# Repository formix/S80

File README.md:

# S80
## S80 - Stackable retro Z80 computer
Welcome to the primary source of information regarding the S80.

For in depth information on the S80 hardware, please visit: [S80 website](http://users.telenet.be/pynckels/s80_retro.html)

The S80 facebook page can be found at: [S80 on Facebook](https://www.facebook.com/S80computer)

The issues section of this repository will serve as discussion forum on everything around the S80 (actual and future hardware, actual and future software, inspirational ideas, questions, ...): [S80 community and forum](https://github.com/PaintedBlck/S80/issues)

We hope this is the beginning of a growing community of people around the S80 who want to inspire others, learn, help, discuss, ... See also the Code of Conduct, since this document describes how we see collaboration and having fun.

## S80C - Small Z80 Cp/m computer

This is a project in the making. The first discussions on the functionality have begun on the [S80 community and forum in Issue 12](https://github.com/PaintedBlck/S80/issues/12).

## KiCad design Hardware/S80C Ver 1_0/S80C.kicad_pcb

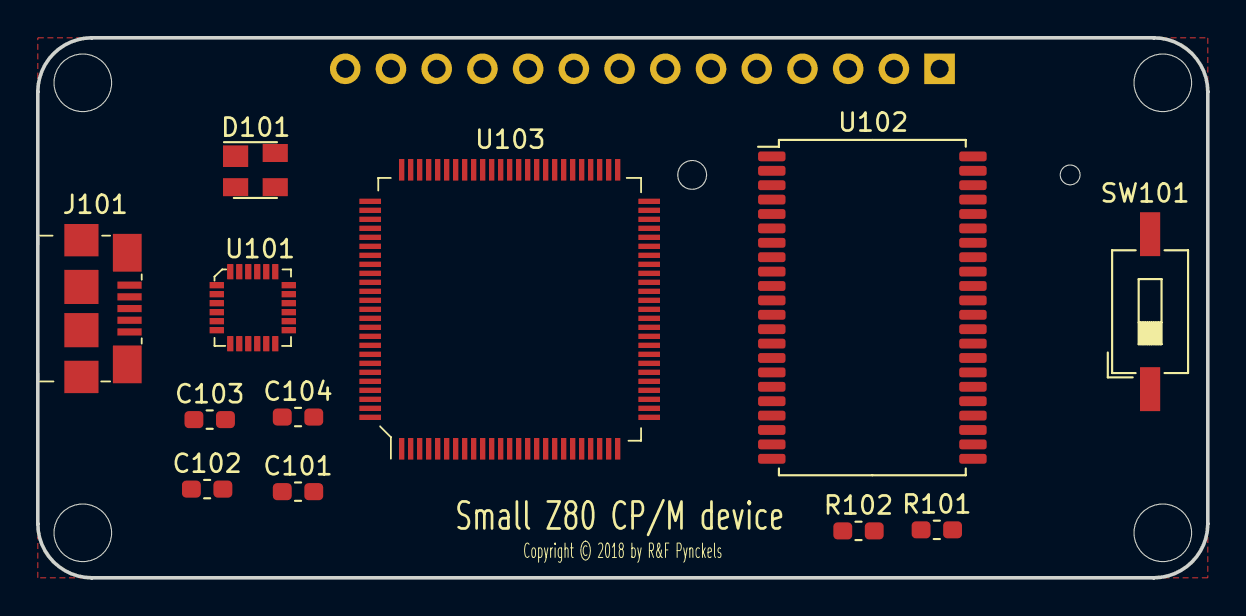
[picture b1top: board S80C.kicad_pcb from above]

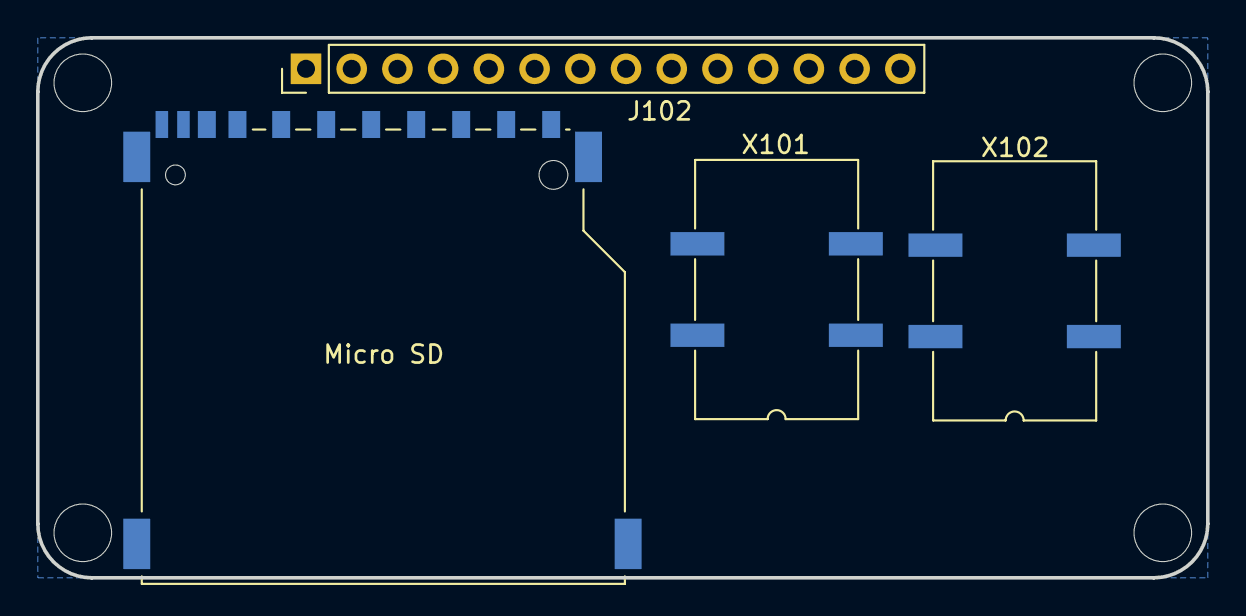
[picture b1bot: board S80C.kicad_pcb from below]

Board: 2 copper layers, 65.0 x 30.0 mm, 16 parts (4 on the bottom side), 64 nets, no tracks yet.

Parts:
C101: 22µF; C_0603_1608Metric_Pad1.05x0.95mm_HandSolder
C102: 2µF; C_0603_1608Metric_Pad1.05x0.95mm_HandSolder
C103: 0.1µF; C_0603_1608Metric_Pad1.05x0.95mm_HandSolder
C104: 1µF; C_0603_1608Metric_Pad1.05x0.95mm_HandSolder
D101: SP0503BAHT; SOT-143
J101: USB; USB_Micro_B_Female_10118192
J102: Conn_01x14_Male; PinHeader_1x14_P2.54mm_Vertical
Micro SD: SD_TE_2041021
R101, R102: 1K 5%; R_0603_1608Metric_Pad1.05x0.95mm_HandSolder
SW101: SW_Push; SW_DIP_SPSTx01_Slide_6.7x4.1mm_W8.61mm_P2.54mm_LowProfile
U101: CP2105; QFN-24-1EP_4x4mm
U102: AS6C8008A; TSOP-II-44_10.16x18.41mm_P0.8mm
U103: eZ80L92; LQFP-100_14x14mm
X101: SG-615PTJ 32Khz; Oscillator_SMD_SeikoEpson_SG8002JA-4Pin_14.0x8.7mm
X102: SG-615PTJ 50Mhz; Oscillator_SMD_SeikoEpson_SG8002JA-4Pin_14.0x8.7mm

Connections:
+3V3: C102.1, C103.1, U101.5, U101.6
/A0: U102.5, U103.1
/A1: U102.4, U103.2
/A2: U102.3, U103.3
/A3: U102.2, U103.4
/A4: U102.1, U103.5
/A5: U102.44, U103.6
/A6: U102.43, U103.9
/A7: U102.42, U103.10
/A8: U102.39, U103.11
/A9: U102.28, U103.12
/A10: U102.27, U103.13
/A11: U102.26, U103.14
/A12: U102.25, U103.15
/A13: U102.24, U103.16
/A14: U102.23, U103.17
/A15: U102.22, U103.20
/A16: U102.21, U103.21
/A17: U102.20, U103.22
/A18: U102.19, U103.23
/A19: U102.18, U103.24
/CTSe: U101.10, U103.78
/CTSs: U101.18, U103.70
/D0: U102.9, U103.35
/D1: U102.10, U103.36
/D2: U102.13, U103.37
/D3: U102.14, U103.38
/D4: U102.31, U103.39
/D5: U102.32, U103.40
/D6: U102.35, U103.41
/D7: U102.36, U103.42
/DSRe: U101.14, U103.80
/DSRs: U101.22, U103.72
/DTRe: U101.15, U103.81
/DTRs: U101.23, U103.73
/GPIO0: J102.3, U103.88
/GPIO1: J102.4, U103.89
/GPIO2: J102.5, U103.90
/GPIO3: J102.6, U103.91
/GPIO4: J102.7, U103.92
/GPIO5: J102.8, U103.93
/GPIO6: J102.9, U103.94
/GPIO7: J102.10, U103.95
/PC6: J102.11, U103.82
/PC7: J102.12, U103.83
/PD6: J102.13, U103.74
/PD7: J102.14, U103.75
/RTC_XIN: U103.58, X101.3
/RTSe: U101.11, U103.79
/RTSs: U101.19, U103.71
/RxDe: U101.12, U103.76
/RxDs: U101.20, U103.68
/TxDe: U101.13, U103.77
/TxDs: U101.21, U103.69
/XIN: U103.85, X102.3
/~MREQ: U102.6, U103.46
/~RESET: C101.1, R102.1, U101.9, U103.51
/~WR: U102.17, U103.48
GND: C101.2, C102.2, C103.2, C104.2, J101.5, J102.2, SW101.1, U101.2, U102.12, U102.34, U103.8, U103.19, U103.34, U103.44, U103.57, U103.61, U103.84, U103.97, X101.2, X102.2
unnamed: D101.1, J101.4
unnamed: D101.2, J101.2, U101.4
unnamed: D101.3, J101.3, U101.3
unnamed: R101.1, R102.2, SW101.2
VCC: C104.1, D101.4, J101.1, J102.1, R101.2, U101.7, U101.8, U102.11, U102.33, U102.40, U103.7, U103.18, U103.33, U103.43, U103.56, U103.60, U103.67, U103.87, U103.96, X101.1, X101.4, X102.1, X102.4

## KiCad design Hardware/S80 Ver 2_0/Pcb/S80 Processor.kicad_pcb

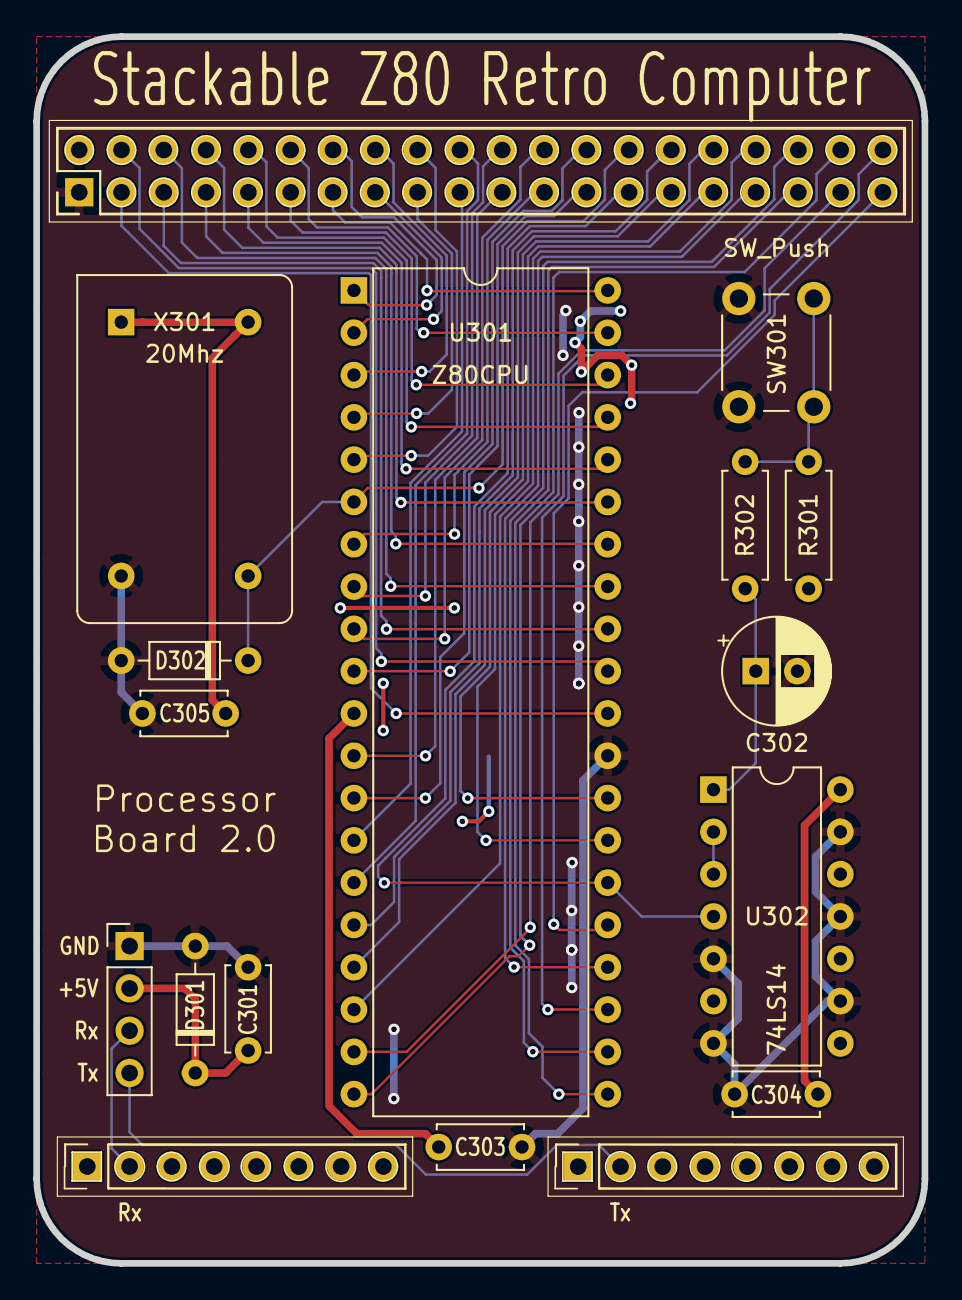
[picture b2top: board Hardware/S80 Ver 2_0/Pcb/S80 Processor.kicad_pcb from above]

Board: 2 copper layers, 53.3 x 73.7 mm, 17 parts (0 on the bottom side), 45 nets.

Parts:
C301, C303, C304, C305: 100pf; C_Disc_D5.0mm_W2.5mm_P5.00mm
C302: 22μF; CP_Radial_D6.3mm_P2.50mm
D301, D302: 5V1; D_Zener_Reverse_Biased
J301, J303: 01x08; PinSocket_1x08_P2.54mm_Vertical
J302: 02x20; PinSocket_2x20_P2.54mm_Vertical
J304: 01x04; PinHeader_1x04_P2.54mm_Vertical
R301, R302: 1K 5%; R_Axial_DIN0207_L6.3mm_D2.5mm_P7.62mm_Horizontal
SW301: SW_Push; SW_PUSH_6mm
U301: Z80CPU; DIP-40_W15.24mm
U302: 74LS14; DIP-14_W7.62mm
X301: 20Mhz; Oscillator_DIP-14

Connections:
/Memory/A0: J302.3, U301.30
/Memory/A1: J302.4, U301.31
/Memory/A2: J302.5, U301.32
/Memory/A3: J302.6, U301.33
/Memory/A4: J302.7, U301.34
/Memory/A5: J302.8, U301.35
/Memory/A6: J302.9, U301.36
/Memory/A7: J302.10, U301.37
/Memory/A8: J302.11, U301.38
/Memory/A9: J302.12, U301.39
/Memory/A10: J302.13, U301.40
/Memory/A11: J302.14, U301.1
/Memory/A12: J302.15, U301.2
/Memory/A13: J302.16, U301.3
/Memory/A14: J302.17, U301.4
/Memory/A15: J302.18, U301.5
/Memory/C8: J302.35, U301.21
/Memory/C9: J302.36, U301.22
/Memory/C10: J302.37, U301.19
/Memory/D0: J302.19, U301.14
/Memory/D1: J302.20, U301.15
/Memory/D2: J302.21, U301.12
/Memory/D3: J302.22, U301.8
/Memory/D4: J302.23, U301.7
/Memory/D5: J302.24, U301.9
/Memory/D6: J302.25, U301.10
/Memory/D7: J302.26, U301.13
/Processor/C0: J302.27, U301.26, U302.4
/Processor/C1: D302.2, J302.28, U301.6, X301.8
/Processor/C2: J302.29, U301.17
/Processor/C3: J302.30, U301.16
/Processor/C4: J302.31, U301.27
/Processor/C5: J302.32, U301.28
/Processor/C6: J302.33, U301.24
/Processor/C7: J302.34, U301.18
/Processor/C11: J302.38, U301.20
/Processor/C12: J302.39, U301.25
/Processor/C13: J302.40, U301.23
/Processor/Rx: J301.2, J304.3
/Processor/Tx: J303.2, J304.4
GND: C301.1, C302.2, C303.1, C304.1, C305.1, D301.1, D302.1, J302.1, J304.1, SW301.1, U301.29, U302.5, U302.7, U302.9, U302.11, U302.13, X301.7
unnamed: C302.1, R302.1, U302.1
unnamed: R301.2, R302.2, SW301.2
unnamed: U302.2, U302.3
VCC: C301.2, C303.2, C304.2, C305.2, D301.2, J302.2, J304.2, R301.1, U301.11, U302.14, X301.1, X301.14

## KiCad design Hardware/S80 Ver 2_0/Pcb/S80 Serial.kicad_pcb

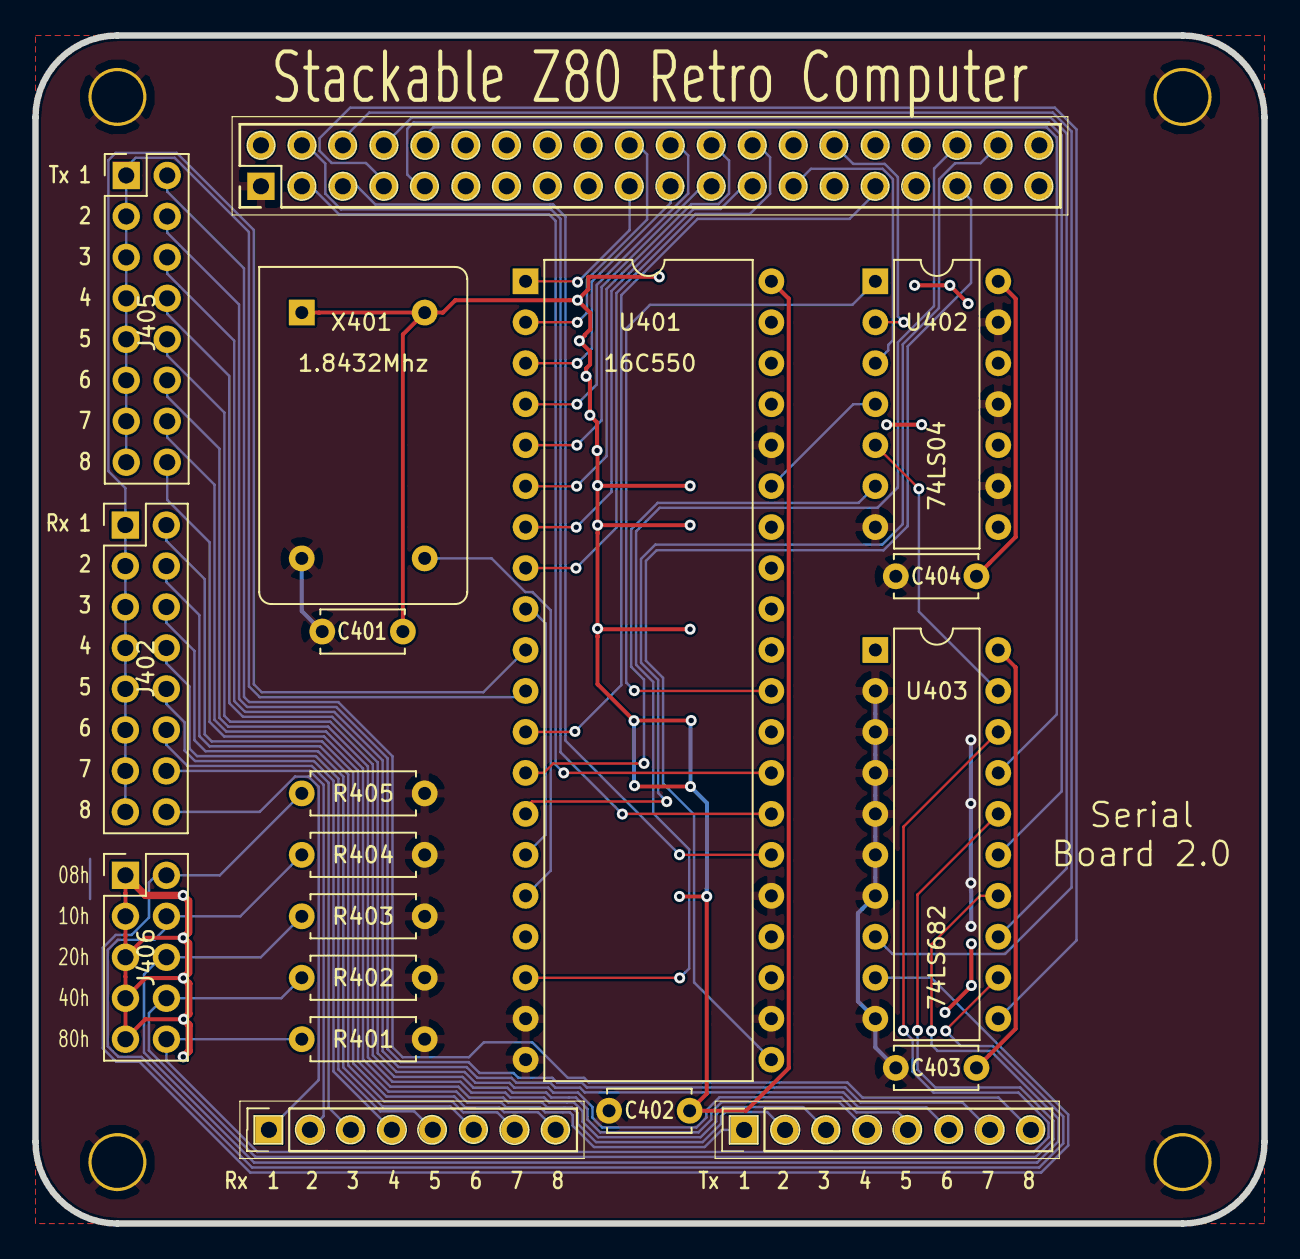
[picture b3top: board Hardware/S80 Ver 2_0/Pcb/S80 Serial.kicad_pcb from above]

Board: 2 copper layers, 76.2 x 73.7 mm, 23 parts (0 on the bottom side), 53 nets.

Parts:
C401, C402, C403, C404: 100pf; C_Disc_D5.0mm_W2.5mm_P5.00mm
H401, H402, H403, H404: Mh_Pad; MountingHole_3.2mm_Via
J401, J404: 01x08; PinSocket_1x08_P2.54mm_Vertical
J402, J405: 02x08; PinHeader_2x08_P2.54mm_Vertical
J403: 02x20; PinSocket_2x20_P2.54mm_Vertical
J406: 02x05; PinHeader_2x05_P2.54mm_Vertical
R401, R402, R403, R404, R405: 5K 5%; R_Axial_DIN0207_L6.3mm_D2.5mm_P7.62mm_Horizontal
U401: 16C550; DIP-40_W15.24mm
U402: 74LS04; DIP-14_W7.62mm
U403: 74LS682; DIP-20_W7.62mm
X401: 1.8432Mhz; Oscillator_DIP-14

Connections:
/Memory/A0: J403.3, U401.28
/Memory/A1: J403.4, U401.27
/Memory/A2: J403.5, U401.26
/Memory/A3: J403.6, U403.8
/Memory/A4: J403.7, U403.11
/Memory/A5: J403.8, U403.13
/Memory/A6: J403.9, U403.15
/Memory/A7: J403.10, U403.17
/Memory/C8: J403.35, U401.21
/Memory/C9: J403.36, U401.18
/Memory/D0: J403.19, U401.1
/Memory/D1: J403.20, U401.2
/Memory/D2: J403.21, U401.3
/Memory/D3: J403.22, U401.4
/Memory/D4: J403.23, U401.5
/Memory/D5: J403.24, U401.6
/Memory/D6: J403.25, U401.7
/Memory/D7: J403.26, U401.8
/Processor/C0: J403.27, U402.3
/Processor/C3: J403.30, U402.2
/Processor/C4: J403.31, U401.12
/Processor/C11: J403.38, U401.14
/Processor/Rx: J402.1, J402.3, J402.5, J402.7, J402.9, J402.11, J402.13, J402.15, U401.10
/Processor/Tx: J405.1, J405.3, J405.5, J405.7, J405.9, J405.11, J405.13, J405.15, U401.11
GND: C401.1, C402.1, C403.1, C404.1, H401.1, H402.1, H403.1, H404.1, J403.1, R401.2, R402.2, R403.2, R404.2, R405.2, U401.19, U401.20, U401.22, U401.25, U401.36, U402.7, U402.9, U402.11, U402.13, U403.2, U403.3, U403.4, U403.5, U403.6, U403.7, U403.10, X401.7
unnamed: J401.1, J402.16
unnamed: J401.2, J402.14
unnamed: J401.3, J402.12
unnamed: J401.4, J402.10
unnamed: J401.5, J402.8
unnamed: J401.6, J402.6
unnamed: J401.7, J402.4
unnamed: J401.8, J402.2
unnamed: J404.1, J405.16
unnamed: J404.2, J405.14
unnamed: J404.3, J405.12
unnamed: J404.4, J405.10
unnamed: J404.5, J405.8
unnamed: J404.6, J405.6
unnamed: J404.7, J405.4
unnamed: J404.8, J405.2
unnamed: J406.2, R405.1, U403.9
unnamed: J406.4, R404.1, U403.12
unnamed: J406.6, R403.1, U403.14
unnamed: J406.8, R402.1, U403.16
unnamed: J406.10, R401.1, U403.18
unnamed: U401.13, U402.6
unnamed: U401.9, U401.15
unnamed: U401.16, X401.8
unnamed: U401.30, U402.1
unnamed: U401.35, U402.4
unnamed: U402.5, U403.19
VCC: C401.2, C402.2, C403.2, C404.2, J403.2, J406.1, J406.3, J406.5, J406.7, J406.9, U401.40, U402.14, U403.20, X401.1, X401.14

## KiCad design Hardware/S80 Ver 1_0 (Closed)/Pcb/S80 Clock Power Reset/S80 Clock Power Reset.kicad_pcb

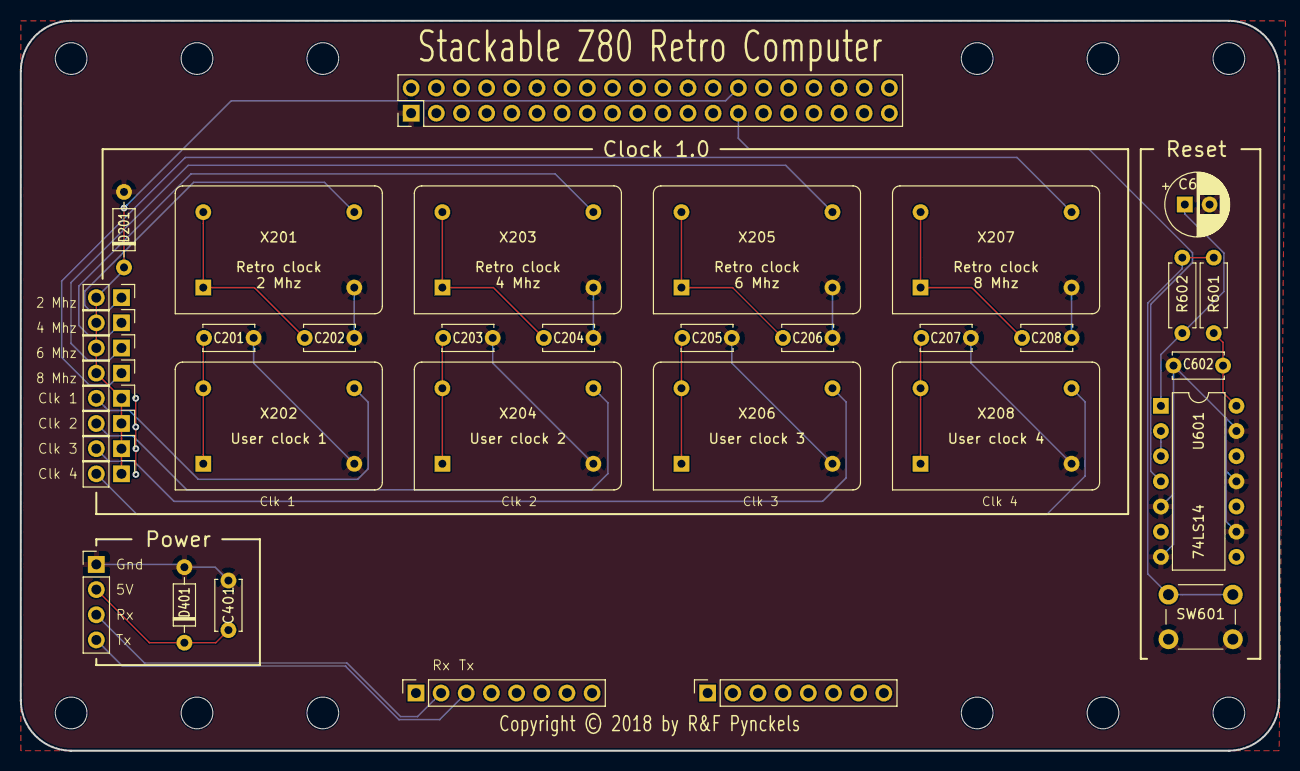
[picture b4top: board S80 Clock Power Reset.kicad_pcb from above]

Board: 2 copper layers, 127.0 x 73.7 mm, 37 parts (0 on the bottom side), 17 nets.

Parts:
C201, C202, C203, C204, C205, C206, C207, C208, C401, C602: 100pf; C_Disc_D5.0mm_W2.5mm_P5.00mm
C601: 22μF; CP_Radial_D6.3mm_P2.50mm
D201, D401: 5V1; D_Zener_Reverse_Biased
J201: 02x20; PinSocket_2x20_P2.54mm_Vertical
J402, J403: 01x08; PinSocket_1x08_P2.54mm_Vertical
J404: 01x04; PinHeader_1x04_P2.54mm_Vertical
JP201, JP202, JP203, JP204, JP205, JP206, JP207, JP208: 01x02; PinHeader_1x02_P2.54mm_Vertical
R601, R602: 1K; R_Axial_DIN0207_L6.3mm_D2.5mm_P7.62mm_Horizontal
SW601: SW_Push; SW_PUSH_6mm
U601: 74LS14; DIP-14_W7.62mm
X201: 2.5Mhz; Oscillator_DIP-14
X202: User clk 1; Oscillator_DIP-14
X203: 4Mhz; Oscillator_DIP-14
X204: User clk 2; Oscillator_DIP-14
X205: 6Mhz; Oscillator_DIP-14
X206: User clk 3; Oscillator_DIP-14
X207: 8Mhz; Oscillator_DIP-14
X208: User clk 4; Oscillator_DIP-14

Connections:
/Breakout 2in/C0: J201.27, U601.4
/Breakout 2in/C1: D201.2, J201.28, JP201.2, JP202.1, JP203.2, JP204.1, JP205.2, JP206.1, JP207.2, JP208.1
/Power/Rx: J402.2, J404.3
/Power/Tx: J402.3, J404.4
GND: C201.1, C202.1, C203.1, C204.1, C205.1, C206.1, C207.1, C208.1, C401.1, C601.2, C602.1, D201.1, D401.1, J201.1, J404.1, SW601.1, U601.5, U601.7, U601.9, U601.11, U601.13, X201.7, X202.7, X203.7, X204.7, X205.7, X206.7, X207.7, X208.7
unnamed: C601.1, R602.1, U601.1
unnamed: JP201.1, X201.8
unnamed: JP202.2, X202.8
unnamed: JP203.1, X203.8
unnamed: JP204.2, X204.8
unnamed: JP205.1, X205.8
unnamed: JP206.2, X206.8
unnamed: JP207.1, X207.8
unnamed: JP208.2, X208.8
unnamed: R601.2, R602.2, SW601.2
unnamed: U601.2, U601.3
VCC: C201.2, C202.2, C203.2, C204.2, C205.2, C206.2, C207.2, C208.2, C401.2, C602.2, D401.2, J201.2, J404.2, R601.1, U601.14, X201.1, X201.14, X202.1, X202.14, X203.1, X203.14, X204.1, X204.14, X205.1, X205.14, X206.1, X206.14, X207.1, X207.14, X208.1, X208.14

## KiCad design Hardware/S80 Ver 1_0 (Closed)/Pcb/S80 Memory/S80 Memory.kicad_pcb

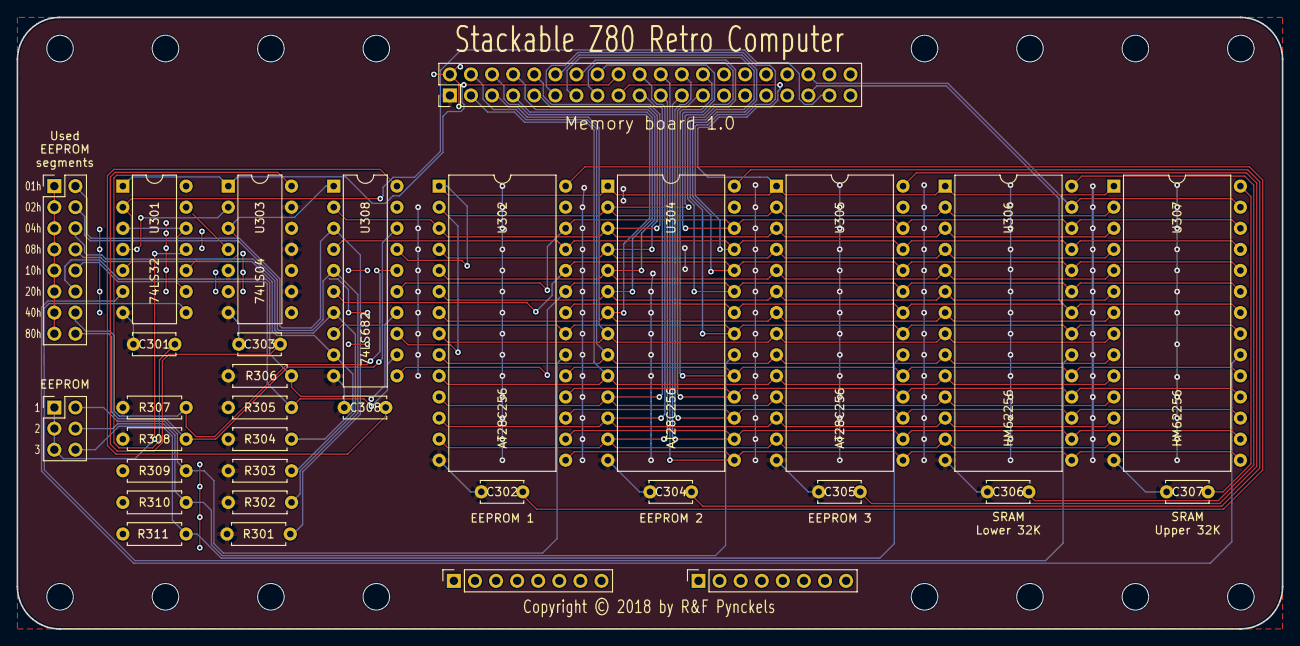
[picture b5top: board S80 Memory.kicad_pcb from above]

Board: 2 copper layers, 152.4 x 73.7 mm, 32 parts (0 on the bottom side), 47 nets.

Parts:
C301, C302, C303, C304, C305, C306, C307, C308: 100pf; C_Disc_D5.0mm_W2.5mm_P5.00mm
J301: 02x20; PinSocket_2x20_P2.54mm_Vertical
J302, J303: 01x08; PinSocket_1x08_P2.54mm_Vertical
J304: 02x08; PinHeader_2x08_P2.54mm_Vertical
J305: 02x03; PinHeader_2x03_P2.54mm_Vertical
R301, R302, R303, R304, R305, R306, R307, R308: 220 5%; R_Axial_DIN0207_L6.3mm_D2.5mm_P7.62mm_Horizontal
R309, R310, R311: 5K 1%; R_Axial_DIN0207_L6.3mm_D2.5mm_P7.62mm_Horizontal
U301: 74LS32; DIP-14_W7.62mm
U302, U304, U305: AT28C256; DIP-28_W15.24mm
U303: 74LS04; DIP-14_W7.62mm
U306, U307: HM62256; DIP-28_W15.24mm
U308: 74LS682; DIP-20_W7.62mm

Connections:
/Breakout 2in/A0: J301.3, U302.10, U304.10, U305.10, U306.10, U307.10
/Breakout 2in/A1: J301.4, U302.9, U304.9, U305.9, U306.9, U307.9
/Breakout 2in/A2: J301.5, U302.8, U304.8, U305.8, U306.8, U307.8
/Breakout 2in/A3: J301.6, U302.7, U304.7, U305.7, U306.7, U307.7
/Breakout 2in/A4: J301.7, U302.6, U304.6, U305.6, U306.6, U307.6
/Breakout 2in/A5: J301.8, U302.5, U304.5, U305.5, U306.5, U307.5
/Breakout 2in/A6: J301.9, U302.4, U304.4, U305.4, U306.4, U307.4
/Breakout 2in/A7: J301.10, U302.3, U304.3, U305.3, U306.3, U307.3, U308.2
/Breakout 2in/A8: J301.11, U302.25, U304.25, U305.25, U306.25, U307.25, U308.4
/Breakout 2in/A9: J301.12, U302.24, U304.24, U305.24, U306.24, U307.24, U308.6
/Breakout 2in/A10: J301.13, U302.21, U304.21, U305.21, U306.21, U307.21, U308.8
/Breakout 2in/A11: J301.14, U302.23, U304.23, U305.23, U306.23, U307.23, U308.11
/Breakout 2in/A12: J301.15, U302.2, U304.2, U305.2, U306.2, U307.2, U308.13
/Breakout 2in/A13: J301.16, U302.26, U304.26, U305.26, U306.26, U307.26, U308.15
/Breakout 2in/A14: J301.17, U302.1, U304.1, U305.1, U306.1, U307.1, U308.17
/Breakout 2in/A15: J301.18, U301.1, U303.1
/Breakout 2in/C8: J301.35, U302.22, U304.22, U305.22, U306.22, U307.22
/Breakout 2in/C9: J301.36, U306.27, U307.27
/Breakout 2in/C10: J301.37, U301.2, U301.5
/Breakout 2in/D0: J301.19, U302.11, U304.11, U305.11, U306.11, U307.11
/Breakout 2in/D1: J301.20, U302.12, U304.12, U305.12, U306.12, U307.12
/Breakout 2in/D2: J301.21, U302.13, U304.13, U305.13, U306.13, U307.13
/Breakout 2in/D3: J301.22, U302.15, U304.15, U305.15, U306.15, U307.15
/Breakout 2in/D4: J301.23, U302.16, U304.16, U305.16, U306.16, U307.16
/Breakout 2in/D5: J301.24, U302.17, U304.17, U305.17, U306.17, U307.17
/Breakout 2in/D6: J301.25, U302.18, U304.18, U305.18, U306.18, U307.18
/Breakout 2in/D7: J301.26, U302.19, U304.19, U305.19, U306.19, U307.19
/Memory/~A15: U301.4, U303.2
/Memory/~EpL0~: J305.2, R309.2, U302.20
/Memory/~EpL1~: J305.4, R310.2, U304.20
/Memory/~EpL2~: J305.6, R311.2, U305.20
/Memory/~EpL~: J305.1, J305.3, J305.5, U301.11
/Memory/~RaL~: U301.8, U306.20
/Memory/~RaU~: U301.6, U307.20
GND: C301.1, C302.1, C303.1, C304.1, C305.1, C306.1, C307.1, C308.1, J301.1, R301.2, R302.2, R303.2, R304.2, R305.2, R306.2, R307.2, R308.2, U301.7, U302.14, U303.5, U303.7, U303.9, U303.11, U303.13, U304.14, U305.14, U306.14, U307.14, U308.10
unnamed: J304.2, R301.1, U308.3
unnamed: J304.4, R302.1, U308.5
unnamed: J304.6, R303.1, U308.7
unnamed: J304.8, R304.1, U308.9
unnamed: J304.10, R305.1, U308.12
unnamed: J304.12, R306.1, U308.14
unnamed: J304.14, R307.1, U308.16
unnamed: J304.16, R308.1, U308.18
unnamed: U301.10, U303.3, U308.1
unnamed: U301.3, U301.9, U301.12
unnamed: U301.13, U303.4
VCC: C301.2, C302.2, C303.2, C304.2, C305.2, C306.2, C307.2, C308.2, J301.2, J304.1, J304.3, J304.5, J304.7, J304.9, J304.11, J304.13, J304.15, R309.1, R310.1, R311.1, U301.14, U302.27, U302.28, U303.14, U304.27, U304.28, U305.27, U305.28, U306.28, U307.28, U308.20

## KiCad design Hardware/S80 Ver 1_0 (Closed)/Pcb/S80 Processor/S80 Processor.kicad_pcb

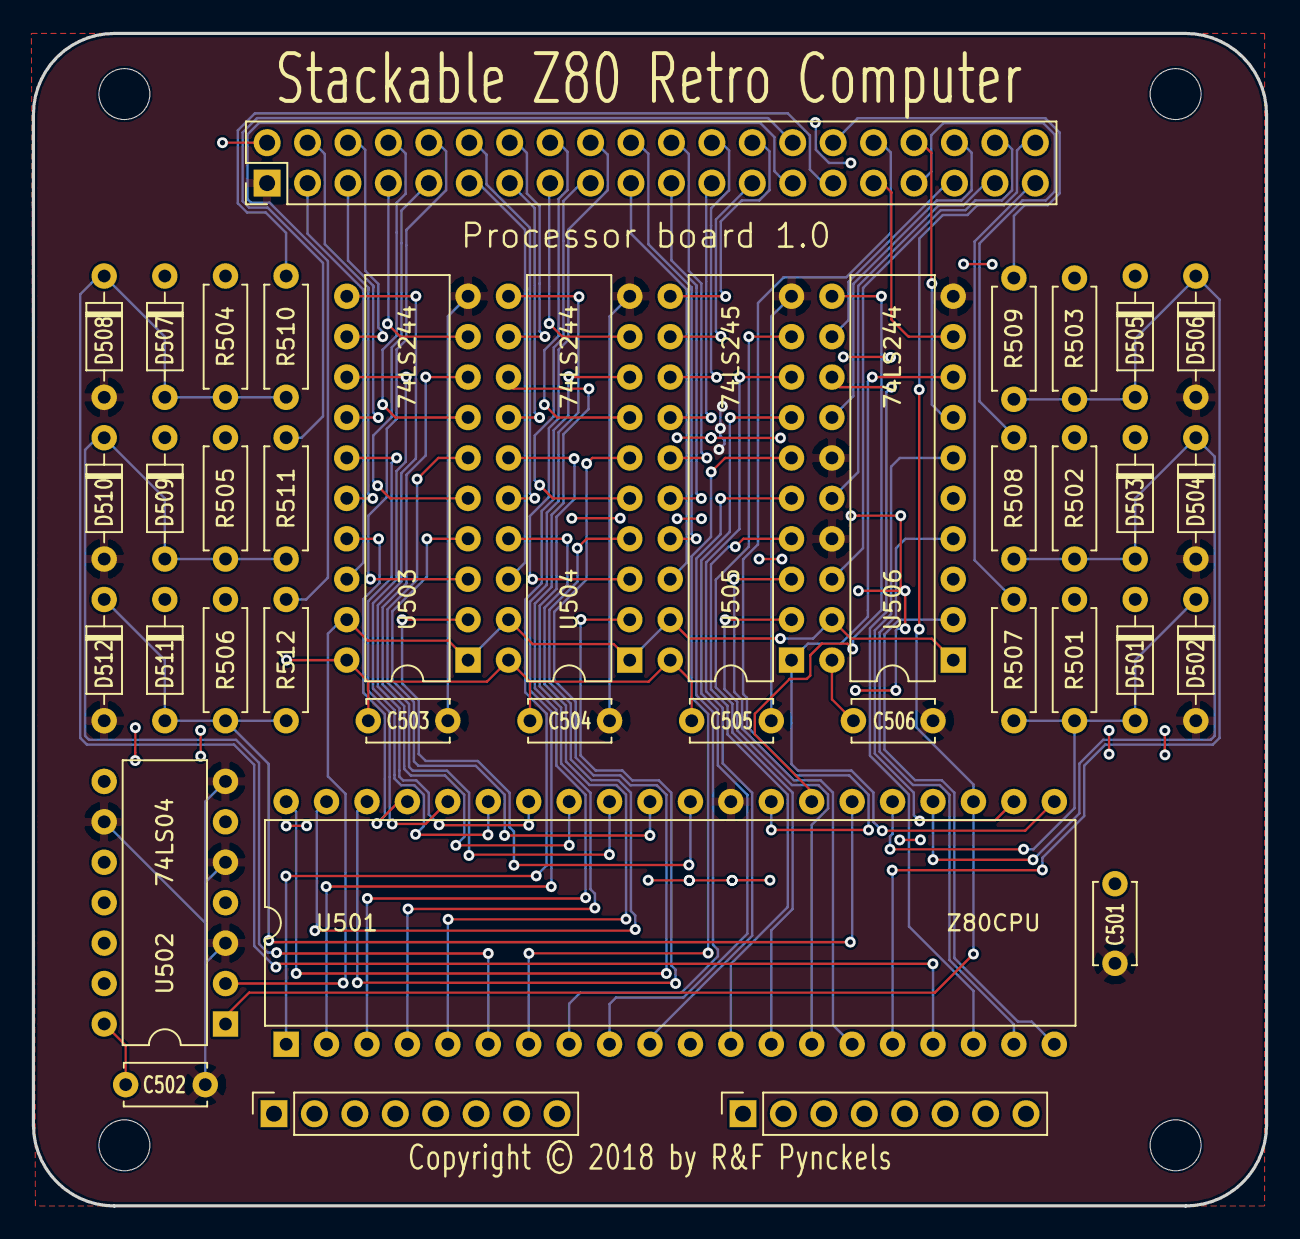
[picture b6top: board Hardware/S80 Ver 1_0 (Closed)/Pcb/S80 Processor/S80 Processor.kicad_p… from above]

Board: 2 copper layers, 77.5 x 73.7 mm, 39 parts (0 on the bottom side), 77 nets.

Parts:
C501, C502, C503, C504, C505, C506: 100pf; C_Disc_D5.0mm_W2.5mm_P5.00mm
D501, D502, D503, D504, D505, D506, D507, D508, D509, D510, D511, D512: D; D_1N4148_Reverse_Biased
J501: 02x20; PinSocket_2x20_P2.54mm_Vertical
J502, J503: 01x08; PinSocket_1x08_P2.54mm_Vertical
R501, R502, R503, R504, R505, R506: 1K; R_Axial_DIN0207_L6.3mm_D2.5mm_P7.62mm_Horizontal
R507, R508, R509, R510, R511, R512: 220; R_Axial_DIN0207_L6.3mm_D2.5mm_P7.62mm_Horizontal
U501: Z80CPU; DIP-40_W15.24mm
U502: 74LS04; DIP-14_W7.62mm
U503, U504, U506: 74LS244; DIP-20_W7.62mm
U505: 74LS245; DIP-20_W7.62mm

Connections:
/Breakout 2in/A0: J501.3, U503.18
/Breakout 2in/A1: J501.4, U503.16
/Breakout 2in/A2: J501.5, U503.14
/Breakout 2in/A3: J501.6, U503.12
/Breakout 2in/A4: J501.7, U503.9
/Breakout 2in/A5: J501.8, U503.7
/Breakout 2in/A6: J501.9, U503.5
/Breakout 2in/A7: J501.10, U503.3
/Breakout 2in/A8: J501.11, U504.18
/Breakout 2in/A9: J501.12, U504.16
/Breakout 2in/A10: J501.13, U504.14
/Breakout 2in/A11: J501.14, U504.12
/Breakout 2in/A12: J501.15, U504.9
/Breakout 2in/A13: J501.16, U504.7
/Breakout 2in/A14: J501.17, U504.5
/Breakout 2in/A15: J501.18, U504.3
/Breakout 2in/C0: J501.27, R512.1
/Breakout 2in/C1: J501.28, R511.1
/Breakout 2in/C2: J501.29, R510.1
/Breakout 2in/C3: J501.30, R509.1
/Breakout 2in/C4: J501.31, U506.9
/Breakout 2in/C5: J501.32, U501.28
/Breakout 2in/C6: J501.33, R508.1
/Breakout 2in/C7: J501.34, U506.7
/Breakout 2in/C8: J501.35, U506.12
/Breakout 2in/C9: J501.36, U506.14
/Breakout 2in/C10: J501.37, U506.16
/Breakout 2in/C11: J501.38, U506.18
/Breakout 2in/C12: J501.39, R507.1
/Breakout 2in/C13: J501.40, U501.23, U502.1
/Breakout 2in/D0: J501.19, U505.18
/Breakout 2in/D1: J501.20, U505.17
/Breakout 2in/D2: J501.21, U505.16
/Breakout 2in/D3: J501.22, U505.15
/Breakout 2in/D4: J501.23, U505.14
/Breakout 2in/D5: J501.24, U505.13
/Breakout 2in/D6: J501.25, U505.12
/Breakout 2in/D7: J501.26, U505.11
/Processor/Out: U502.2, U503.1, U503.19, U504.1, U504.19, U505.19, U506.1, U506.19
/Processor/ZA0: U501.30, U503.2
/Processor/ZA1: U501.31, U503.4
/Processor/ZA2: U501.32, U503.6
/Processor/ZA3: U501.33, U503.8
/Processor/ZA4: U501.34, U503.11
/Processor/ZA5: U501.35, U503.13
/Processor/ZA6: U501.36, U503.15
/Processor/ZA7: U501.37, U503.17
/Processor/ZA8: U501.38, U504.2
/Processor/ZA9: U501.39, U504.4
/Processor/ZA10: U501.40, U504.6
/Processor/ZA11: U501.1, U504.8
/Processor/ZA12: U501.2, U504.11
/Processor/ZA13: U501.3, U504.13
/Processor/ZA14: U501.4, U504.15
/Processor/ZA15: U501.5, U504.17
/Processor/ZD0: U501.14, U505.2
/Processor/ZD1: U501.15, U505.3
/Processor/ZD2: U501.12, U505.4
/Processor/ZD3: U501.8, U505.5
/Processor/ZD4: U501.7, U505.6
/Processor/ZD5: U501.9, U505.7
/Processor/ZD6: U501.10, U505.8
/Processor/ZD7: U501.13, U505.9
/Processor/~BusRq: D501.1, D502.2, R501.2, R507.2, U501.25
/Processor/~CLK: D509.1, D510.2, R505.2, R511.2, U501.6
/Processor/~Halt: U501.18, U506.13
/Processor/~INT: D505.1, D506.2, R503.2, R509.2, U501.16
/Processor/~IOrq: U501.20, U506.2
/Processor/~M1: U501.27, U506.11
/Processor/~Mreq: U501.19, U506.4
/Processor/~NMI: D507.1, D508.2, R504.2, R510.2, U501.17
/Processor/~RD: U501.21, U505.1, U506.8
/Processor/~Reset: D511.1, D512.2, R506.2, R512.2, U501.26
/Processor/~WR: U501.22, U506.6
/Processor/~Wait: D503.1, D504.2, R502.2, R508.2, U501.24
GND: C501.1, C502.1, C503.1, C504.1, C505.1, C506.1, D502.1, D504.1, D506.1, D508.1, D510.1, D512.1, J501.1, U501.29, U502.3, U502.5, U502.7, U502.9, U503.10, U504.10, U505.10, U506.10, U506.15, U506.17
VCC: C501.2, C502.2, C503.2, C504.2, C505.2, C506.2, D501.2, D503.2, D505.2, D507.2, D509.2, D511.2, J501.2, R501.1, R502.1, R503.1, R504.1, R505.1, R506.1, U501.11, U502.14, U503.20, U504.20, U505.20, U506.20

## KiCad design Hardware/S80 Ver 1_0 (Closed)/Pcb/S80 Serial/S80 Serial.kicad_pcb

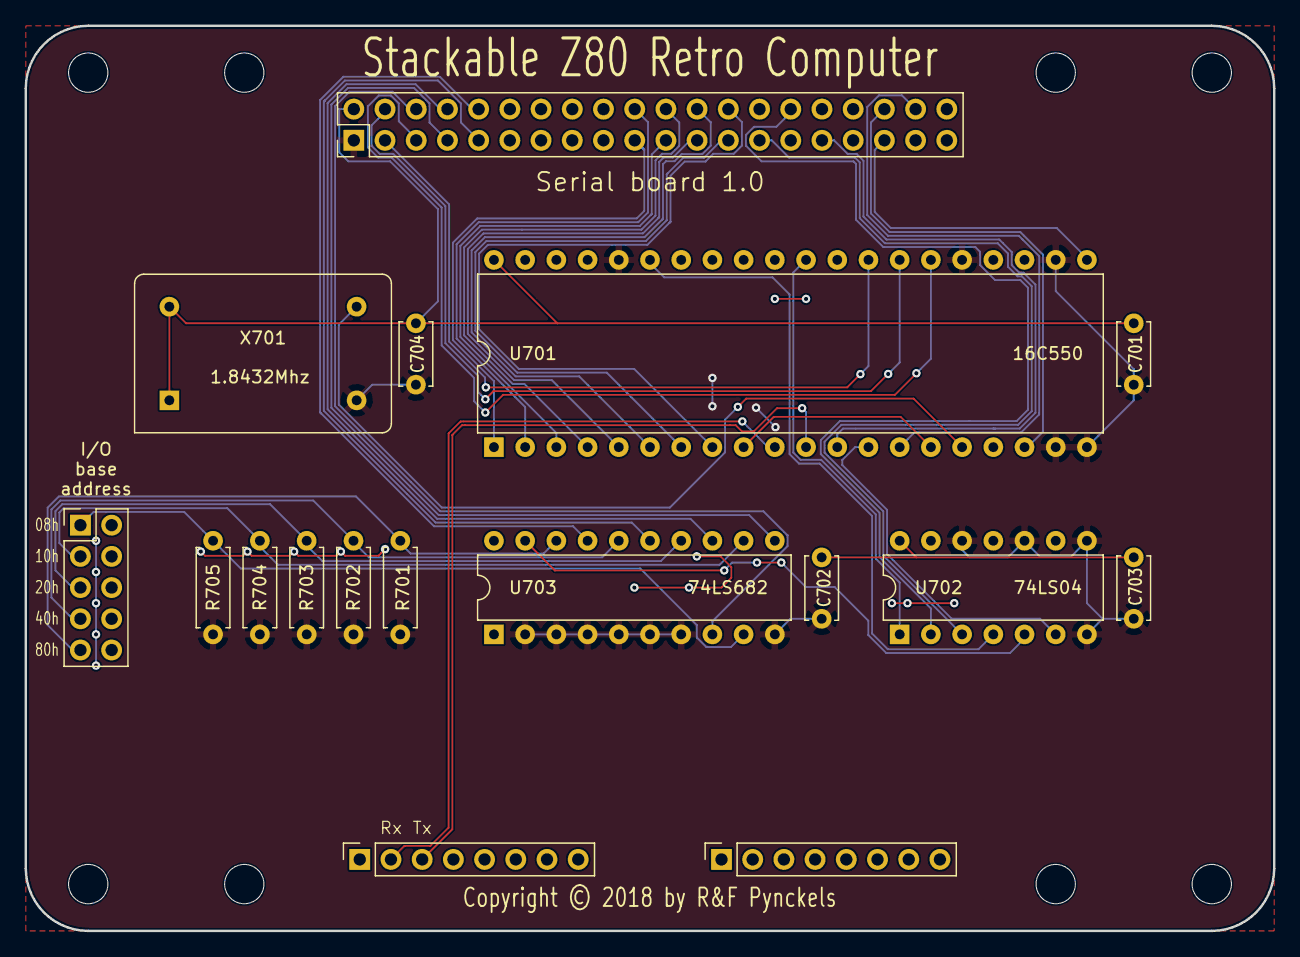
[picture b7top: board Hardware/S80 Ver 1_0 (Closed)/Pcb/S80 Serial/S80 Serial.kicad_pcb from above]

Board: 2 copper layers, 101.6 x 73.7 mm, 17 parts (0 on the bottom side), 37 nets.

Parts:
C701, C702, C703, C704: 100pf; C_Disc_D5.0mm_W2.5mm_P5.00mm
J701: 02x20; PinSocket_2x20_P2.54mm_Vertical
J702, J703: 01x08; PinSocket_1x08_P2.54mm_Vertical
J704: 02x05; PinHeader_2x05_P2.54mm_Vertical
R701, R702, R703, R704, R705: 5K; R_Axial_DIN0207_L6.3mm_D2.5mm_P7.62mm_Horizontal
U701: 16C550; DIP-40_W15.24mm
U702: 74LS04; DIP-14_W7.62mm
U703: 74LS682; DIP-20_W7.62mm
X701: 1.8432Mhz; Oscillator_DIP-14

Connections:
/Breakout 2in/A0: J701.3, U701.28
/Breakout 2in/A1: J701.4, U701.27
/Breakout 2in/A2: J701.5, U701.26
/Breakout 2in/A3: J701.6, U703.8
/Breakout 2in/A4: J701.7, U703.11
/Breakout 2in/A5: J701.8, U703.13
/Breakout 2in/A6: J701.9, U703.15
/Breakout 2in/A7: J701.10, U703.17
/Breakout 2in/C0: J701.27, U702.3
/Breakout 2in/C3: J701.30, U702.2
/Breakout 2in/C4: J701.31, U701.12
/Breakout 2in/C8: J701.35, U701.21
/Breakout 2in/C9: J701.36, U701.18
/Breakout 2in/C11: J701.38, U701.14
/Breakout 2in/D0: J701.19, U701.1
/Breakout 2in/D1: J701.20, U701.2
/Breakout 2in/D2: J701.21, U701.3
/Breakout 2in/D3: J701.22, U701.4
/Breakout 2in/D4: J701.23, U701.5
/Breakout 2in/D5: J701.24, U701.6
/Breakout 2in/D6: J701.25, U701.7
/Breakout 2in/D7: J701.26, U701.8
/Breakout 2in/U1: J702.2, U701.10
/Breakout 2in/U2: J702.3, U701.11
GND: C701.1, C702.1, C703.1, C704.1, J701.1, R701.2, R702.2, R703.2, R704.2, R705.2, U701.19, U701.20, U701.22, U701.25, U701.36, U702.7, U702.8, U702.10, U702.12, U703.2, U703.3, U703.4, U703.5, U703.6, U703.7, U703.10, X701.7
unnamed: J704.1, R705.1, U703.9
unnamed: J704.3, R704.1, U703.12
unnamed: J704.5, R703.1, U703.14
unnamed: J704.7, R702.1, U703.16
unnamed: J704.9, R701.1, U703.18
unnamed: U701.13, U702.6
unnamed: U701.9, U701.15
unnamed: U701.16, X701.8
unnamed: U701.30, U702.1
unnamed: U701.35, U702.4
unnamed: U702.5, U703.19
VCC: C701.2, C702.2, C703.2, C704.2, J701.2, J704.2, J704.4, J704.6, J704.8, J704.10, U701.40, U702.14, U703.20, X701.1, X701.14

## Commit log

2018-11-04 Directory reorganisation
2018-11-04 Reorganisation
2018-11-04 Introduction of the S80C discussions
2018-11-05 Update Towers of Hanoi
2018-11-05 Update Microcode
2018-11-05 Update S80C design
2018-11-07 Refresh S80 Kicad version (5.01)
2018-11-09 Update S80C to S80Z
2018-11-11 Make S80 PCB's and Gerbers public
2018-11-11 Adding Bill of Material
2018-11-12 Reorganisation directory structure
2018-11-17 Add Pynckels-kicad-library
2018-11-17 Reorganisation kicad templates
2018-11-17 Reorganisation Software directory
2018-11-17 Reorganisation Hardware directory
2018-11-22 S80 Ver 1_0 document layout change
2018-11-22 KiCad footprint library update
2018-11-22 Towers of Hanoi insert term.bat
2018-11-22 Repository reorganisation
2018-11-22 S80 Ver 2_0 initial upload
2018-11-25 Reorganisation project structure
2018-11-25 S80 Memory Schematic redesign
2018-11-25 Update kicad library
2018-11-27 Memory 2.0 change
2018-11-29 Memory logic adjustments
2018-12-02 S80 Ver 2_0 circuit design changes
2018-12-02 S80 Ver 2_0 VHDL memory logic simulation

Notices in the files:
Hardware/S80 Ver 1_0 (Closed)/Pcb/S80 Clock Power Reset/S80 Clock Power Reset.kicad_pcb:
Copyright (c) 2018 by R&F Pynckels
Copyright © 2018 by R&F Pynckels
